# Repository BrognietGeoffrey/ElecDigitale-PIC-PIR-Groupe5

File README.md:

# Électronique digitale - PIC/PIR
Projet du cours d'électronique digitale - BAC 2 EPHEC

## Membres du groupe n°5 :

- Baptiste Bemelmans  (@BaptisteBemel)
- Geoffrey Brogniet  (@BrognietGeoffrey)
- Séverin Robert (@severinRobert)
- Lucas Silva (@creativezigzz)
- Mickael Parfondry (@Parfondry)

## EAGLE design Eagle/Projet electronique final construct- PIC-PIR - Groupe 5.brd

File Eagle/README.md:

Bouton poussoir et crystal déjà mis

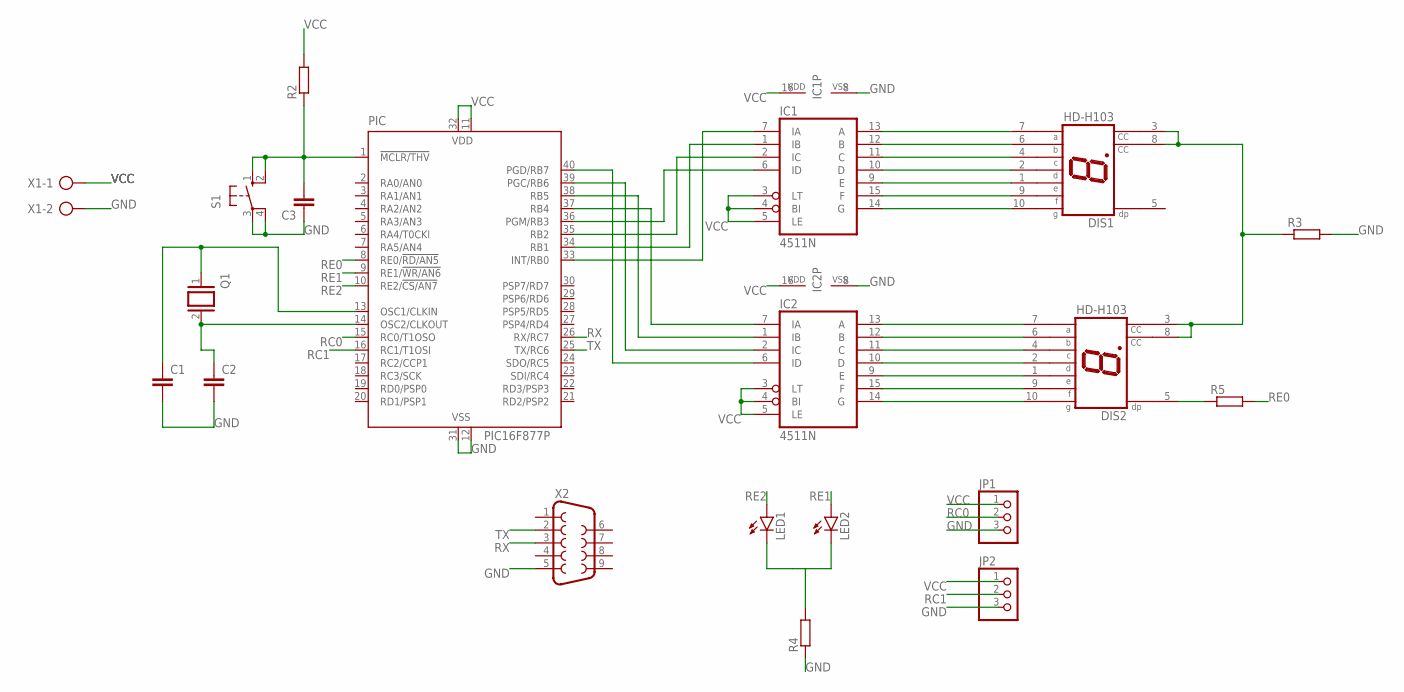
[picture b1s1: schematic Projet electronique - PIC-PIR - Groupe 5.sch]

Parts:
C1, C2, C3: C-EU025-025X050; C025-025X050
DIS1, DIS2: HD-H103; HDSP-M
IC1, IC2: 4511N; DIL16
JP1, JP2: PINHD-1X3; 1X03
LED1, LED2: LED5MM
PIC: PIC16F877P; DIL40
Q1: XTAL/S; QS
R2, R3, R4, R5: R-EU_0207/10; 0207/10
S1: 10-XX; B3F-10XX
X1: AK300/2
X2: F09H

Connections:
GND: C1.2, C2.2, C3.1, IC1.8 (VSS), IC2.8 (VSS), JP1.3, JP2.3, PIC.12 (VSS), PIC.31 (VSS), R3.2, R4.1, S1.3, S1.4 (P1), X1.2, X2.5
unnamed: C2.1, PIC.14 (OSC2/CLKOUT), Q1.2
unnamed: C1.1, PIC.13 (OSC1/CLKIN), Q1.1
unnamed: C3.2, PIC.1 (!MCLR/THV), R2.1, S1.1 (S), S1.2 (S1)
unnamed: IC1.7 (IA), PIC.33 (INT/RB0)
unnamed: IC1.1 (IB), PIC.34 (RB1)
unnamed: IC1.2 (IC), PIC.35 (RB2)
unnamed: IC1.6 (ID), PIC.36 (PGM/RB3)
unnamed: IC2.7 (IA), PIC.37 (RB4)
unnamed: IC2.1 (IB), PIC.38 (RB5)
unnamed: IC2.2 (IC), PIC.39 (PGC/RB6)
unnamed: IC2.6 (ID), PIC.40 (PGD/RB7)
unnamed: DIS1.7 (A), IC1.13 (A)
unnamed: DIS1.6 (B), IC1.12 (B)
unnamed: DIS1.4 (C), IC1.11 (C)
unnamed: DIS1.2 (D), IC1.10 (D)
unnamed: DIS1.1 (E), IC1.9 (E)
unnamed: DIS1.9 (F), IC1.15 (F)
unnamed: DIS1.10 (G), IC1.14 (G)
unnamed: DIS2.7 (A), IC2.13 (A)
unnamed: DIS2.6 (B), IC2.12 (B)
unnamed: DIS2.4 (C), IC2.11 (C)
unnamed: DIS2.2 (D), IC2.10 (D)
unnamed: DIS2.1 (E), IC2.9 (E)
unnamed: DIS2.9 (F), IC2.15 (F)
unnamed: DIS2.10 (G), IC2.14 (G)
unnamed: DIS1.3 (CC), DIS1.8 (CC), DIS2.3 (CC), DIS2.8 (CC), R3.1
unnamed: LED1.K (C), LED2.K (C), R4.2
unnamed: DIS2.5 (DP), R5.1
RC0: JP1.2, PIC.15 (RC0/T1OSO)
RC1: JP2.2, PIC.16 (RC1/T1OSI)
RE0: PIC.8 (RE0/!RD/AN5), R5.2
RE1: LED2.A, PIC.9 (RE1/!WR/AN6)
RE2: LED1.A, PIC.10 (RE2/!CS/AN7)
RX: PIC.26 (RX/RC7), X2.3
TX: PIC.25 (TX/RC6), X2.2
VCC: IC1.3 (LT), IC1.4 (BI), IC1.5 (LE), IC1.16 (VDD), IC2.3 (LT), IC2.4 (BI), IC2.5 (LE), IC2.16 (VDD), JP1.1, JP2.1, PIC.11 (VDD), PIC.32 (VDD), R2.2, X1.1

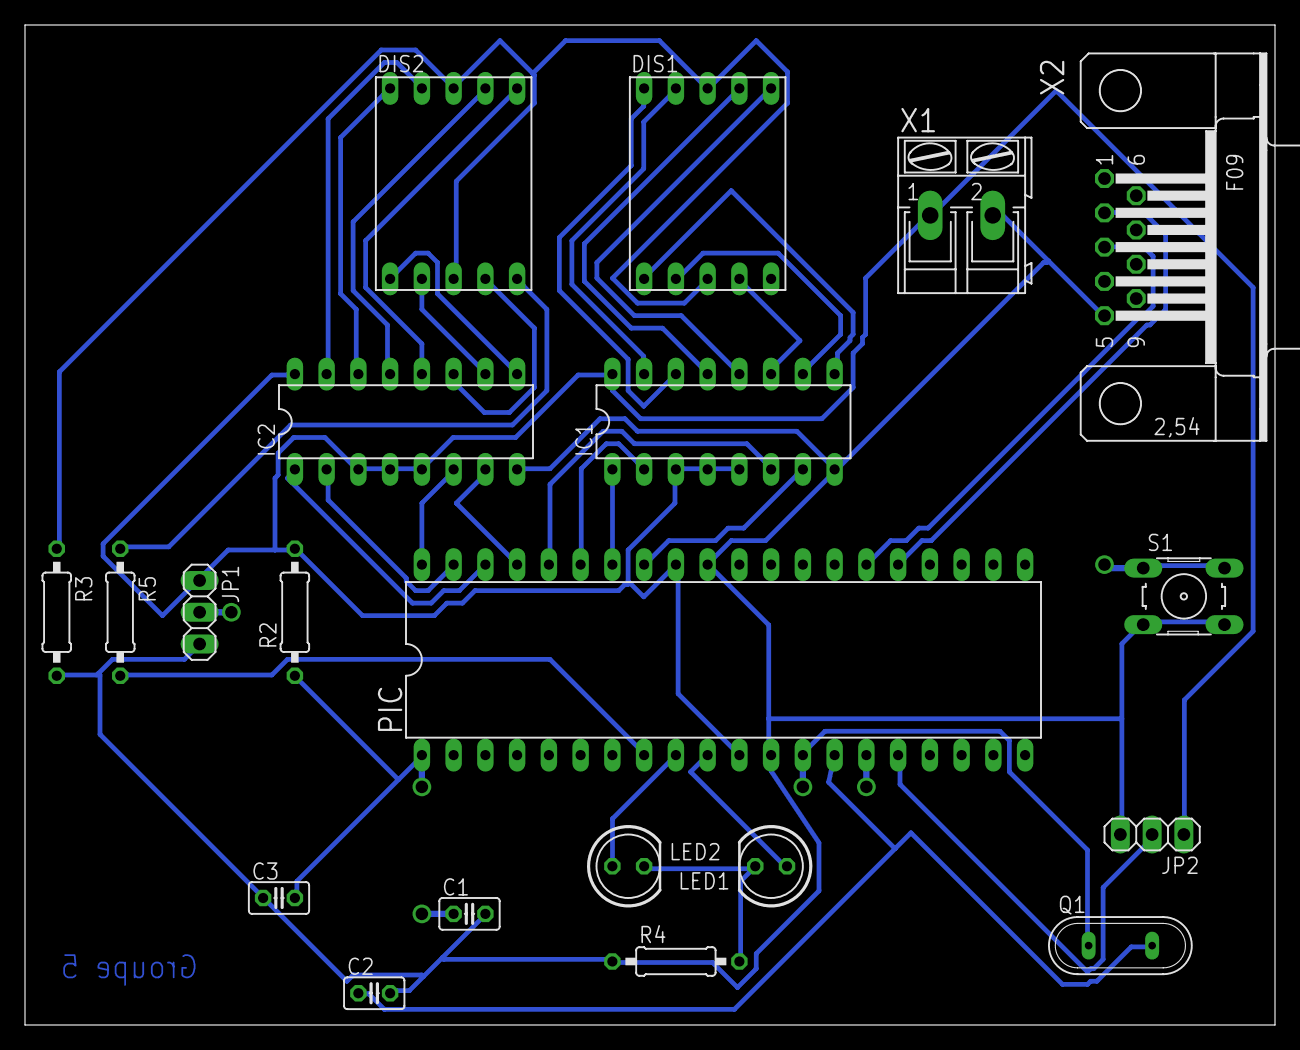
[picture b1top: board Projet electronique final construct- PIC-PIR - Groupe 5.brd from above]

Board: 2 copper layers, 100.0 x 80.0 mm, 20 parts (0 on the bottom side), 37 nets.

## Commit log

2021-03-01 Création infrasctrucure dossiers/fichiers
2021-03-02 Create .c for 18f458
    Juste la création du code pour l'allumage de leds quand le seuil est atteint
2021-03-02 Correction des pir
2021-03-12 Ajout schéma Proteus
2021-03-13 update schéma eagle
2021-03-14 Update file eagle
2021-03-14 update eagle file
2021-03-14 Eagle
2021-03-14 Ajout schéma et board png
2021-03-19 Rajout du PIR manquant
2021-03-19 eagle board
2021-04-23 Schéma final et réorganisation du dossier
2021-04-23 Réorganisation dossier
2021-05-02 encore des erreurs
2021-05-03 printf
2021-05-03 ajout
2021-05-03 ajout setup
2021-05-03 afficheur 7 segment
2021-05-11 Create the guy
2021-05-11 Quelques changements dans le code
2021-05-16 ajout commentaire
2021-05-16 lire data
2021-05-17 Correction de dernière minute
2021-05-17 Correction de dernière minute + ajout pyserial.tar
